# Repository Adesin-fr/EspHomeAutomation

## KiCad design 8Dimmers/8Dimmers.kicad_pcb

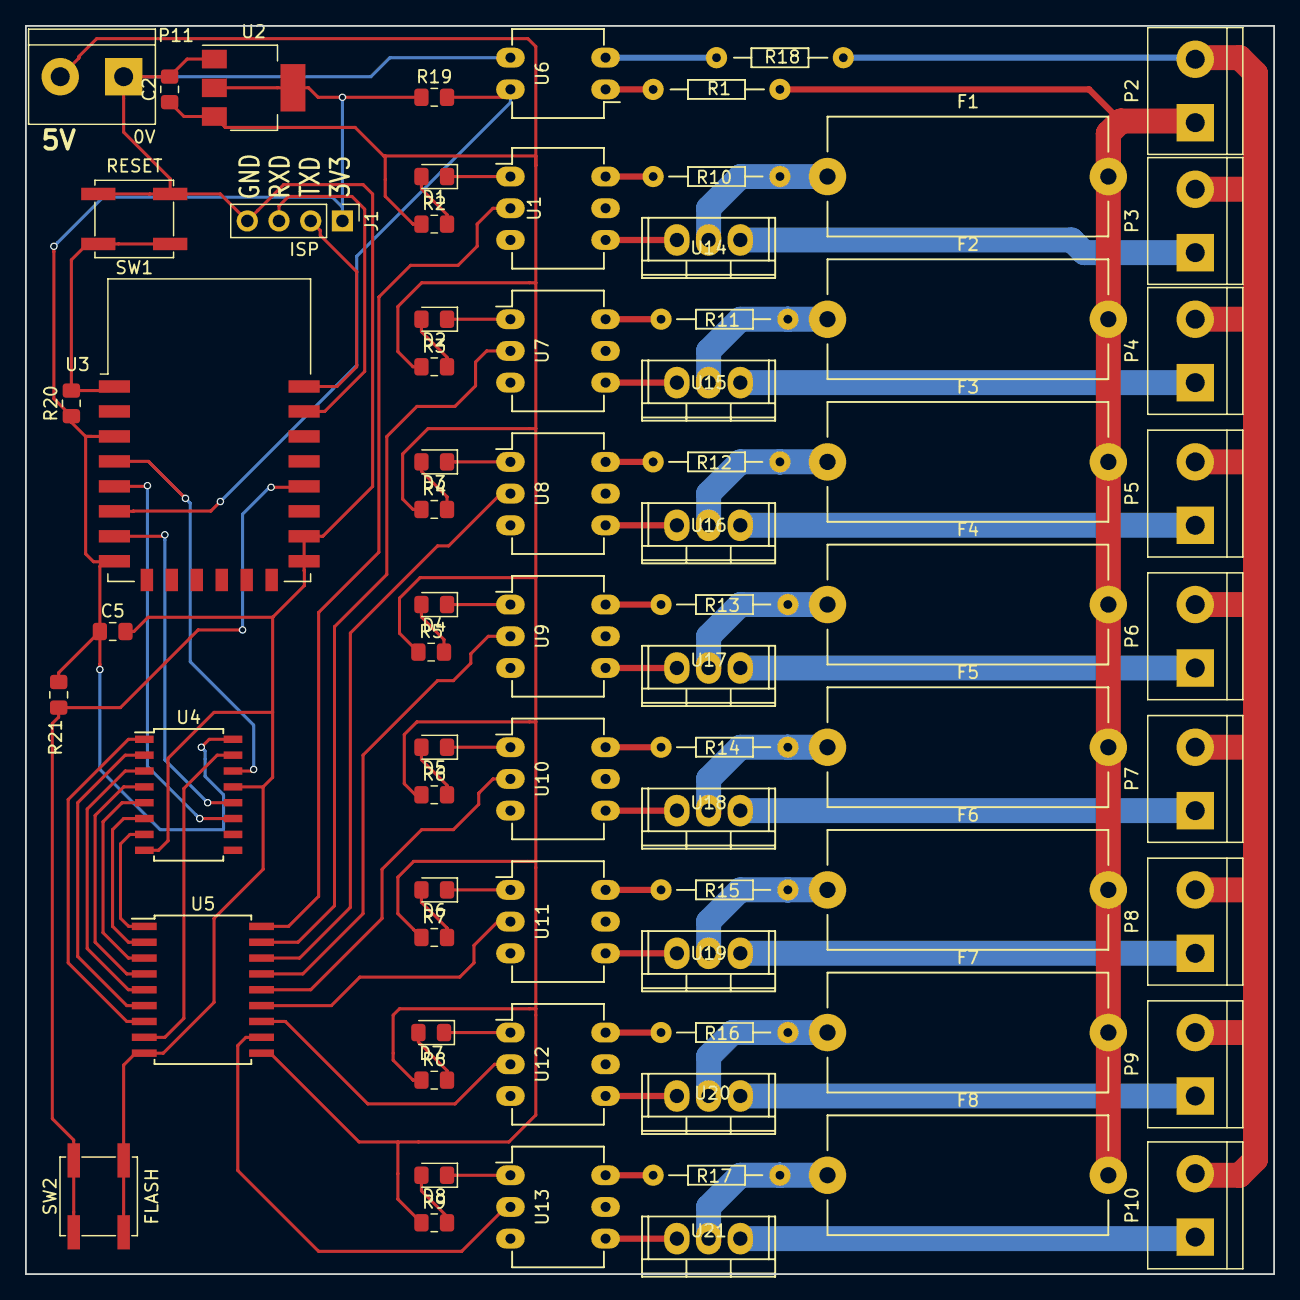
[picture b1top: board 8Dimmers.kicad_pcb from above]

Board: 2 copper layers, 100.0 x 100.0 mm, 73 parts (0 on the bottom side), 79 nets.

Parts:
C2, C5: 100µF; C_0805_2012Metric_Pad1.15x1.40mm_HandSolder
D1, D2, D3, D4, D5, D6, D7, D8: Led; LED_0805_2012Metric_Pad1.15x1.40mm_HandSolder
F1, F2, F3, F4, F5, F6, F7, F8: F_Small; Fuseholder5x20
J1: ISP; PinHeader_1x04_P2.54mm_Vertical
P2, P3, P4, P5, P6, P7, P8, P9, P10: CONN_01X02; TerminalBlock_bornier-2_P5.08mm
P11: 5VIN; TerminalBlock_bornier-2_P5.08mm
R1, R18: 100k; RES35
R2, R3, R4, R5, R6, R7, R8, R9: 100; R_0805_2012Metric_Pad1.15x1.40mm_HandSolder
R10, R11, R12, R13, R14, R15, R16, R17: 4k7; RES35
R19, R20, R21: 10K; R_0805_2012Metric_Pad1.15x1.40mm_HandSolder
SW1: RESET; SW_SPST_EVPBF
SW2: FLASH; SW_SPST_EVPBF
U1: LTV-814; DIP-4_W7.62mm_LongPads
U2: AP1117D33; SOT-223-3_TabPin2
U3: ESP-12F; ESP-12E
U4: 74HC595; SOIC-16W_5.3x10.2mm_P1.27mm
U5: ULN2803A; SOIC-18W_7.5x11.6mm_P1.27mm
U6, U7, U8, U9, U10, U11, U12, U13: MOC3023M; DIP-6_W7.62mm_LongPads
U14, U15, U16, U17, U18, U19, U20, U21: TRIAC_small; TO-220

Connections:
/3V3: C5.1, J1.1, R19.1, R20.1, R21.1, U2.2, U3.3, U3.8, U4.16
/5V: C2.1, P11.2, R2.1, R3.1, R4.1, R5.1, R6.1, R7.1, R8.1, R9.1, U2.3, U5.10
/C0: U5.18, U6.2
/C1: U5.17, U7.2
/C2: U5.16, U8.2
/C3: U5.15, U9.2
/C4: U5.14, U10.2
/C5: U5.13, U11.2
/C6: U5.12, U12.2
/C7: U5.11, U13.2
/GPIO0: R21.2, SW2.1, U3.18
/I1: U4.7, U5.1
/I2: U4.6, U5.2
/I3: U4.5, U5.3
/I4: U4.4, U5.4
/I5: U4.3, U5.5
/I6: U4.2, U5.6
/I7: U4.1, U5.7
/I8: U4.15, U5.8
/N: P2.2, P3.2, P4.2, P5.2, P6.2, P7.2, P8.2, P9.2, P10.2, R18.1
/PH_0: P3.1, U14.1
/PH_1: P4.1, U15.1
/PH_2: P5.1, U16.1
/PH_3: P6.1, U17.1
/PH_4: P7.1, U18.1
/PH_5: P8.1, U19.1
/PH_6: P9.1, U20.1
/PH_7: P10.1, U21.1
/PH_IN: F1.2, F2.2, F3.2, F4.2, F5.2, F6.2, F7.2, F8.2, P2.1, R1.1
/RCLK: U3.7, U4.12
/RST: R20.2, SW1.1, U3.1
/RXD: J1.3, U3.21
/SER: U3.4, U4.14
/SRCLK: U3.5, U4.11
/TXD: J1.2, U3.22
/ZCD: R19.2, U1.4, U3.6
GND: C2.2, C5.2, J1.4, P11.1, SW1.2, SW2.2, U1.3, U2.1, U3.15, U3.16, U4.8, U4.13, U5.9
unnamed: D1.1, U6.1
unnamed: D1.2, R2.2
unnamed: D2.1, U7.1
unnamed: D2.2, R3.2
unnamed: D3.1, U8.1
unnamed: D3.2, R4.2
unnamed: D4.1, U9.1
unnamed: D4.2, R5.2
unnamed: D5.1, U10.1
unnamed: D5.2, R6.2
unnamed: D6.1, U11.1
unnamed: D6.2, R7.2
unnamed: D7.1, U12.1
unnamed: D7.2, R8.2
unnamed: D8.1, U13.1
unnamed: D8.2, R9.2
unnamed: F1.1, R10.2, U14.2
unnamed: F2.1, R11.2, U15.2
unnamed: F3.1, R12.2, U16.2
unnamed: F4.1, R13.2, U17.2
unnamed: F5.1, R14.2, U18.2
unnamed: F6.1, R15.2, U19.2
unnamed: F7.1, R16.2, U20.2
unnamed: F8.1, R17.2, U21.2
unnamed: R1.2, U1.1
unnamed: R10.1, U6.6
unnamed: R11.1, U7.6
unnamed: R12.1, U8.6
unnamed: R13.1, U9.6
unnamed: R14.1, U10.6
unnamed: R15.1, U11.6
unnamed: R16.1, U12.6
unnamed: R17.1, U13.6
unnamed: R18.2, U1.2
unnamed: U10.4, U18.3
unnamed: U11.4, U19.3
unnamed: U12.4, U20.3
unnamed: U13.4, U21.3
unnamed: U6.4, U14.3
unnamed: U7.4, U15.3
unnamed: U8.4, U16.3
unnamed: U9.4, U17.3

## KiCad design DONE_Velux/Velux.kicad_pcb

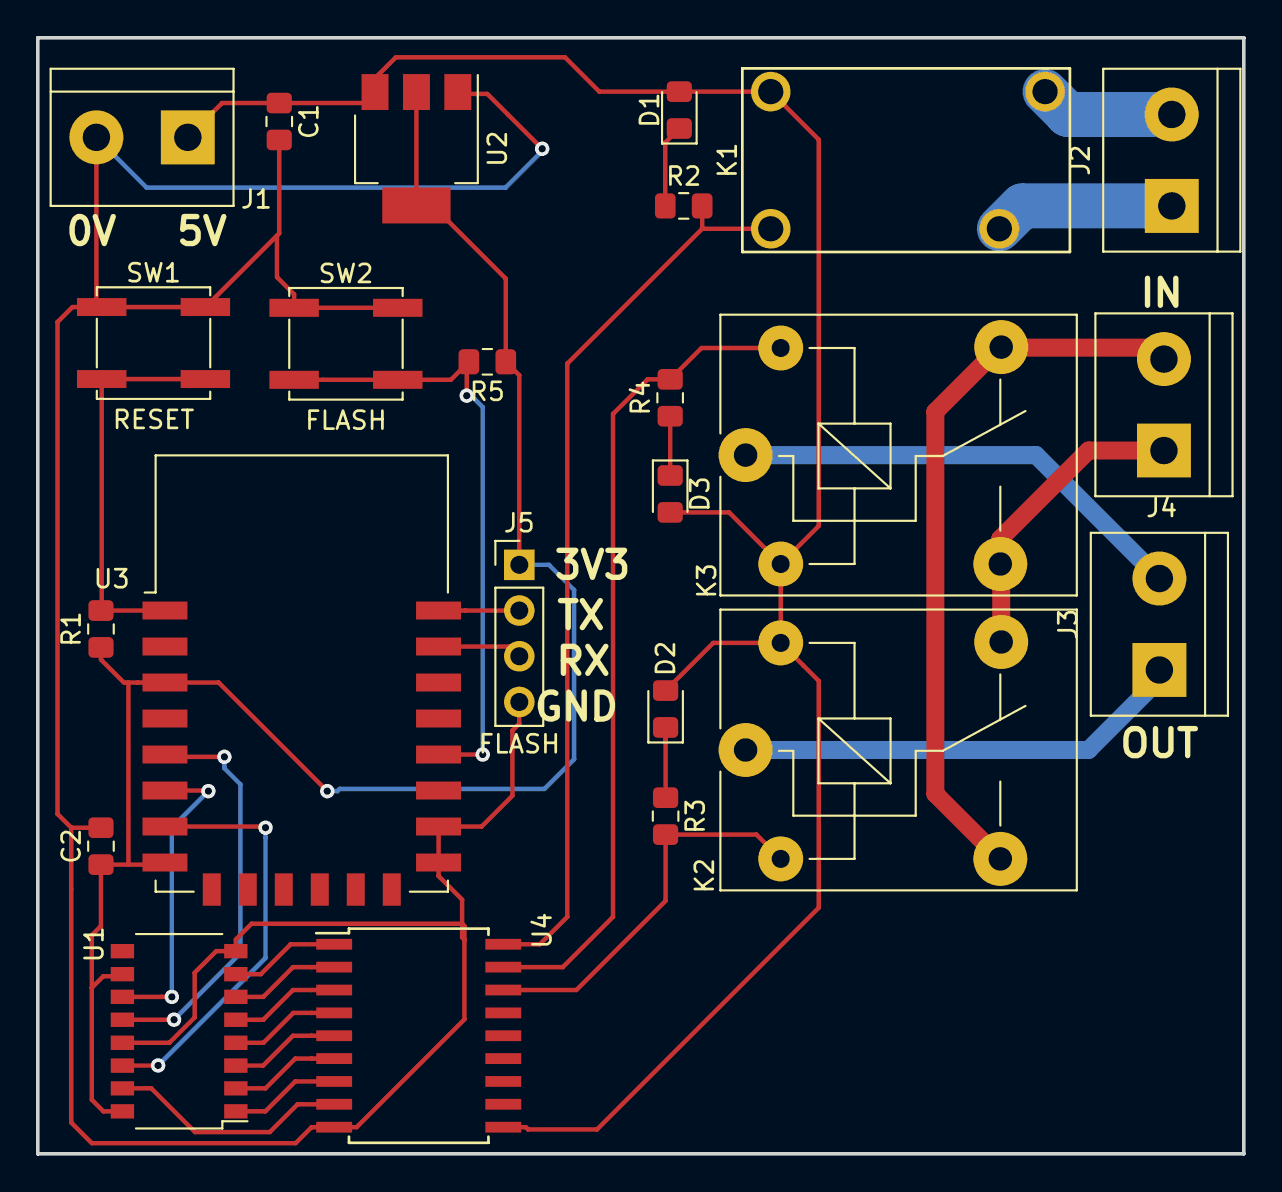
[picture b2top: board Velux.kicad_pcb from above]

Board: 2 copper layers, 67.0 x 62.0 mm, 24 parts (0 on the bottom side), 30 nets.

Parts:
C1: 1uF; C_0805_2012Metric_Pad1.15x1.40mm_HandSolder
C2: 100nF; C_0805_2012Metric_Pad1.15x1.40mm_HandSolder
D1, D2, D3: LED; D_0805_2012Metric_Pad1.15x1.40mm_HandSolder
J1: 5VIN; TerminalBlock_bornier-2_P5.08mm
J2: Conn_01x02_Female; TerminalBlock_bornier-2_P5.08mm
J3: Velux_OUT; TerminalBlock_bornier-2_P5.08mm
J4: 24V_IN; TerminalBlock_bornier-2_P5.08mm
J5: FLASH; PinHeader_1x04_P2.54mm_Vertical
K1: UMS05-1A80-75L; SANYOU-SJ-S
K2, K3: SANYOU_SRD_Form_C; Relay_SPDT_SANYOU_SRD_Series_Form_C
R1: 10k; R_0805_2012Metric_Pad1.15x1.40mm_HandSolder
R2, R3, R4: 290; R_0805_2012Metric_Pad1.15x1.40mm_HandSolder
R5: 10K; R_0805_2012Metric_Pad1.15x1.40mm_HandSolder
SW1: RESET; SW_SPST_EVPBF
SW2: FLASH; SW_SPST_EVPBF
U1: 74HCT595; SOP-16_4.4x10.4mm_P1.27mm
U2: AP1117-33; SOT-223-3_TabPin2
U3: ESP-12F; ESP-12E
U4: ULN2803A; SOIC-18W_7.5x11.6mm_P1.27mm

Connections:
/3V3: C2.1, J5.1, R1.1, R5.1, U1.10, U1.16, U2.2, U3.3, U3.8
/5V: C1.1, D1.2, D2.2, D3.2, J1.1, K1.2, K2.5, K3.2, U2.3, U4.10
/24+: J4.1, K2.4, K3.3
/24-: J4.2, K2.3, K3.4
/GND: C1.2, C2.2, J1.2, J5.4, SW1.1, SW2.1, U1.8, U1.13, U2.1, U3.15, U3.16, U4.9
/GPIO0: R5.2, SW2.2, U3.18
/L1: U1.7, U4.1
/L2: U1.6, U4.2
/L3: U1.5, U4.3
/L4: U1.4, U4.4
/L5: U1.3, U4.5
/L6: U1.2, U4.6
/L7: U1.1, U4.7
/L8: U1.15, U4.8
/OUT1: K1.1, R2.2, U4.18
/OUT2: K3.5, R4.2, U4.17
/OUT3: K2.2, R3.2, U4.16
/RCLK: U1.12, U3.5
/RXD: J5.3, U3.21
/SER: U1.14, U3.7
/SRCLK: U1.11, U3.6
/TXD: J5.2, U3.22
unnamed: D1.1, R2.1
unnamed: D2.1, R3.1
unnamed: D3.1, R4.1
unnamed: J2.1, K1.4
unnamed: J2.2, K1.3
unnamed: J3.1, K2.1
unnamed: J3.2, K3.1
unnamed: R1.2, SW1.2, U3.1

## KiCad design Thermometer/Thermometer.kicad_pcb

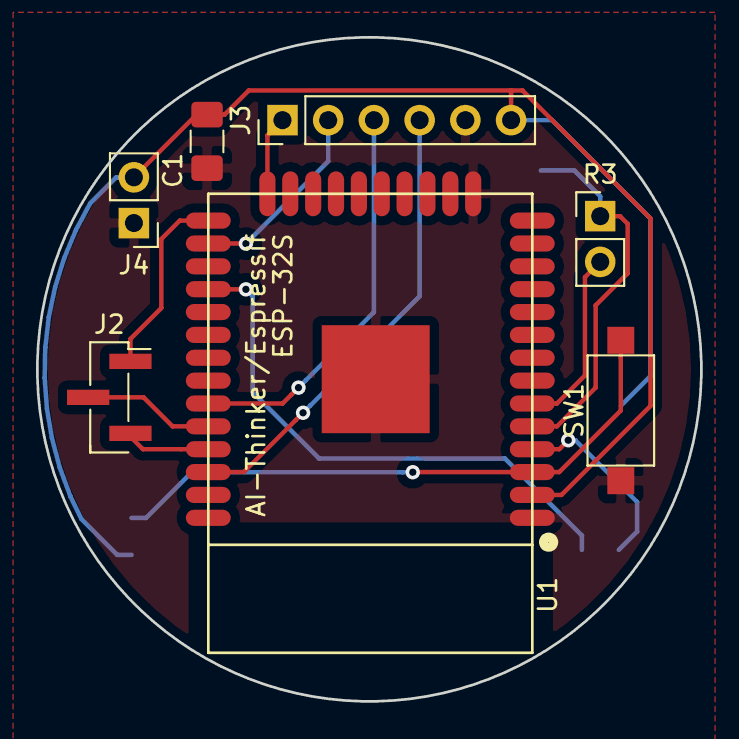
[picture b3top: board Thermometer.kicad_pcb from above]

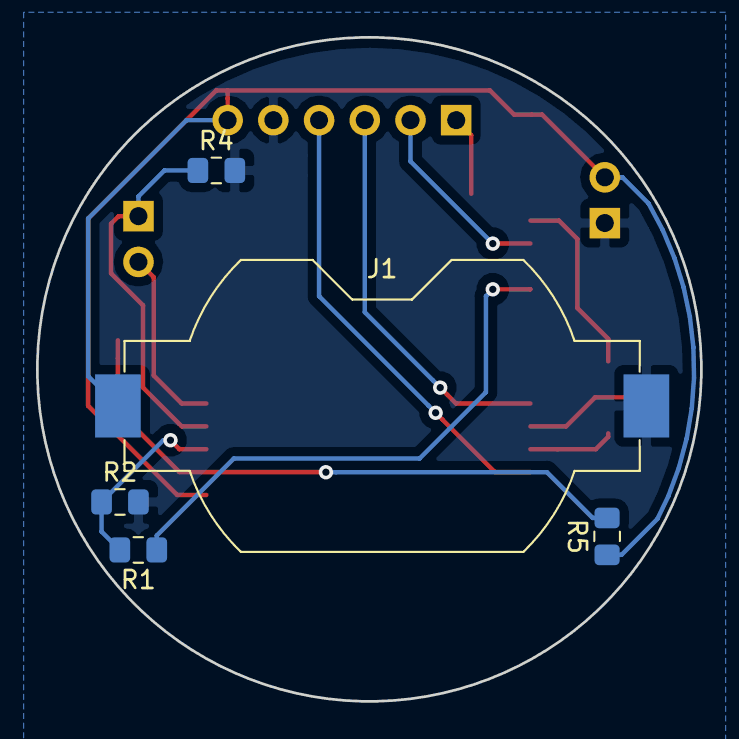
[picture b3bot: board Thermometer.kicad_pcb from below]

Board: 2 copper layers, 36.9 x 36.9 mm, 12 parts (5 on the bottom side), 14 nets.

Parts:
C1: C_Small; C_1206_3216Metric_Pad1.42x1.75mm_HandSolder
J1: Conn_01x02; BatteryHolder_Keystone_1058_1x2032
J2: Conn_01x03; PinHeader_1x03_P2.00mm_Vertical_SMD_Pin1Right
J3: BME280; PinHeader_1x06_P2.54mm_Vertical
J4: Conn_01x02; PinHeader_1x02_P2.54mm_Vertical
R1: 100k; R_0805_2012Metric_Pad1.15x1.40mm_HandSolder
R2: 27K; R_0805_2012Metric_Pad1.15x1.40mm_HandSolder
R3: LDR03; PinHeader_1x02_P2.54mm_Vertical
R4, R5: 10K; R_0805_2012Metric_Pad1.15x1.40mm_HandSolder
SW1: SW_Push; SW_SPST_CK_RS282G05A3
U1: ESP-32S

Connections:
/3V3: C1.1, J1.2, J3.6, J4.2, R5.1, U1.2
/BOOT: J2.1, U1.25
/GND: C1.2, J1.1, J3.5, J4.1, R2.2, R4.2, SW1.1, U1.1, U1.15, U1.39
/IO2: J3.1, U1.24
/IO4: J3.2, U1.26
/LDR_ON: R3.2, U1.6
/RX: J2.2, U1.34
/SCL: J3.4, U1.36
/SDA: J3.3, U1.33
/TX: J2.3, U1.35
/VBAT: R1.2, R2.1, U1.4
/VBAT_ON: R1.1, U1.28
/VLDR: R3.1, R4.1, U1.5
unnamed: R5.2, SW1.2, U1.3
